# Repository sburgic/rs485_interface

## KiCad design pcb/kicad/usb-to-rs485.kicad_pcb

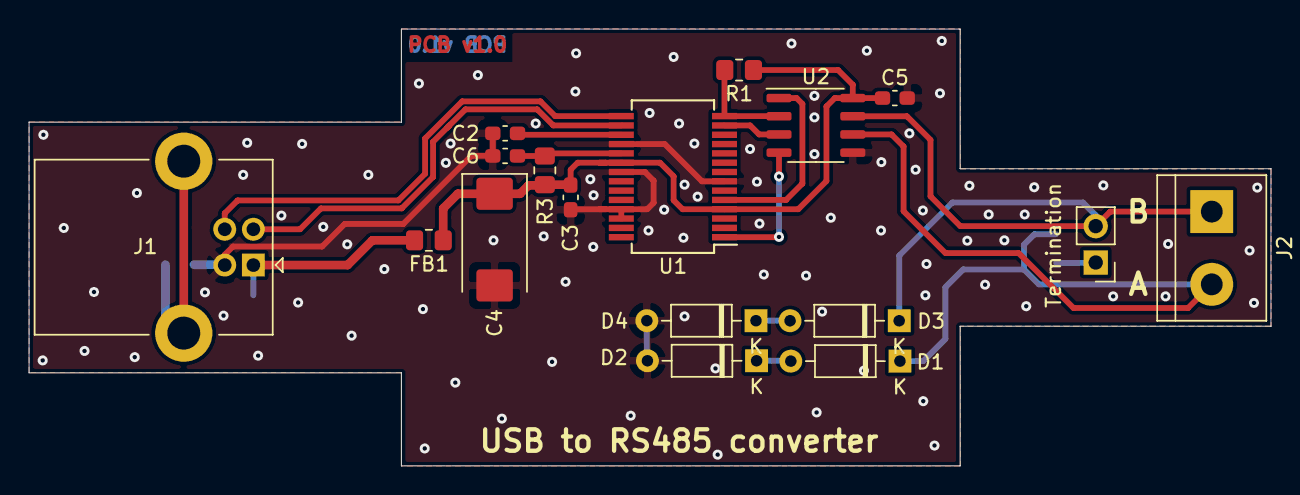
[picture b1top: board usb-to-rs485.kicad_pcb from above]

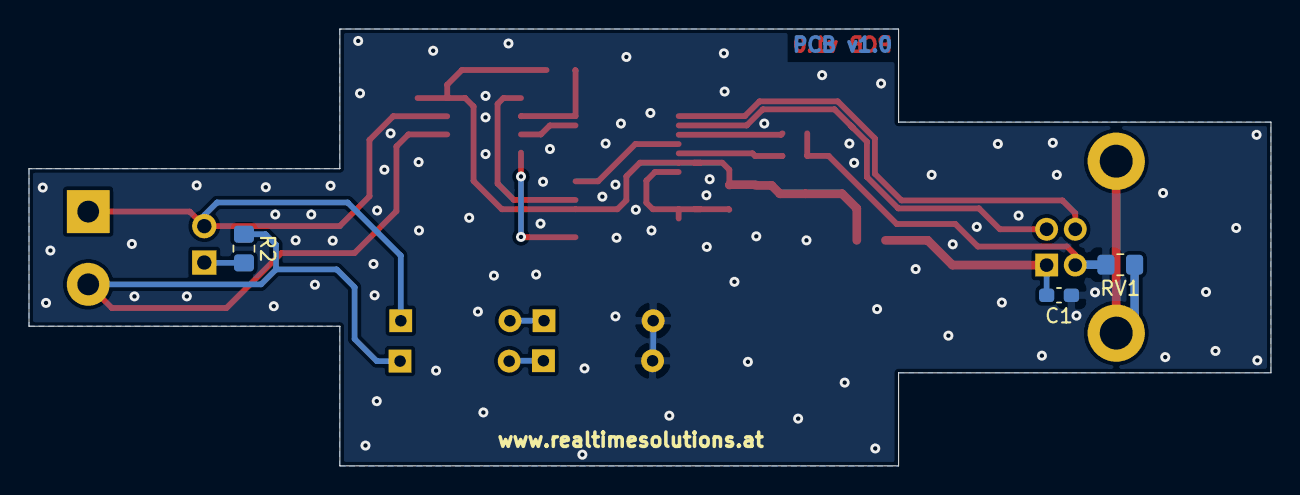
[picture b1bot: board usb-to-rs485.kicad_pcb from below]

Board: 2 copper layers, 86.7 x 30.5 mm, 20 parts (3 on the bottom side), 17 nets.

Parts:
C1: 10nF; C_0603_1608Metric_Pad1.08x0.95mm_HandSolder
C2, C3, C5, C6: 100nF; C_0603_1608Metric_Pad1.08x0.95mm_HandSolder
C4: 4,7uF; CP_EIA-7343-40_Kemet-Y_Pad2.25x2.55mm_HandSolder
D1, D3: 9v1; D_DO-35_SOD27_P7.62mm_Horizontal
D2, D4: 4v7; D_DO-35_SOD27_P7.62mm_Horizontal
FB1: Ferrite_Bead; R_0805_2012Metric_Pad1.20x1.40mm_HandSolder
J1: USB_B; USB_B_Lumberg_2411_02_Horizontal
J2: Screw_Terminal_01x02; TerminalBlock_bornier-2_P5.08mm
JP1: Termination; PinHeader_1x02_P2.54mm_Vertical
R1, R3: 10K; R_0805_2012Metric_Pad1.20x1.40mm_HandSolder
R2: 120R; R_0805_2012Metric_Pad1.20x1.40mm_HandSolder
RV1: Varistor; R_0805_2012Metric_Pad1.20x1.40mm_HandSolder
U1: FT232RL; SSOP-28_5.3x10.2mm_P0.65mm
U2: MAX485E; SO-8_3.9x4.9mm_P1.27mm

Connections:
GND: C1.1, C2.2, C3.1, C4.2, C5.2, C6.1, D2.2, D4.2, J1.4, RV1.2, U1.7, U1.18, U1.21, U1.25, U1.26, U2.5
unnamed: C1.2, FB1.2, J1.1
unnamed: C2.1, U1.17
unnamed: C6.2, R3.1, U1.19
unnamed: D1.1, J2.2, R2.1, U2.6
unnamed: D1.2, D2.1
unnamed: D3.1, J2.1, JP1.2, U2.7
unnamed: D3.2, D4.1
unnamed: J1.2, U1.16
unnamed: J1.3, U1.15
unnamed: J1.5, RV1.1
unnamed: JP1.1, R2.2
unnamed: R1.2, U1.14, U2.2
unnamed: U1.1, U2.4
unnamed: U1.5, U2.1
unnamed: U1.13, U2.3
VCC: C3.2, C4.1, C5.1, FB1.1, R1.1, R3.2, U1.4, U1.20, U2.8

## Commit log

2022-04-27 Add PCB version 1.0
